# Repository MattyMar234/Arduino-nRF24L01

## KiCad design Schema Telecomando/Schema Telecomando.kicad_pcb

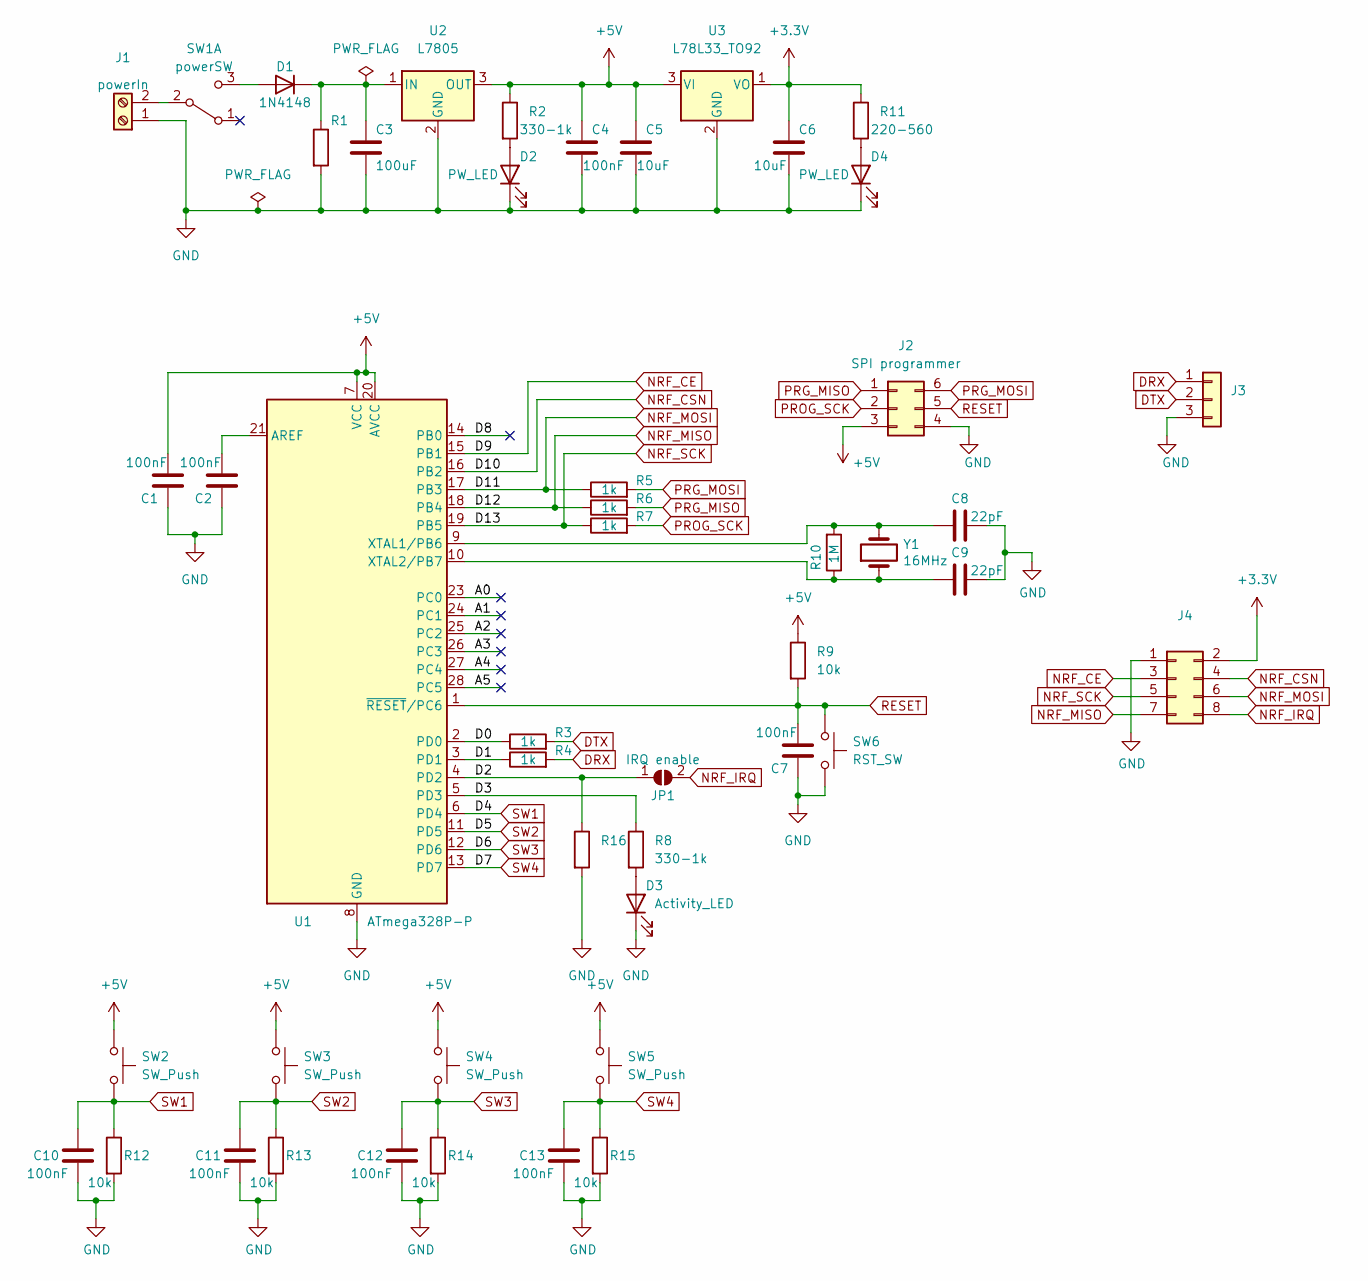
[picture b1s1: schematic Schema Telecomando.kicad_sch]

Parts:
C1, C2, C4, C7, C10, C11, C12, C13: 100nF; C_Disc_D7.0mm_W2.5mm_P5.00mm
C3: 100uF; CP_Radial_D8.0mm_P3.50mm
C5, C6: 10uF; CP_Radial_D8.0mm_P3.50mm
C8, C9: 22pF; C_Disc_D7.0mm_W2.5mm_P5.00mm
D1: 1N4148; D_DO-35_SOD27_P7.62mm_Horizontal
D2, D4: PW_LED; LED_D3.0mm
D3: Activity_LED; LED_D3.0mm
J1: powerIn; TerminalBlock_Altech_AK300-2_P5.00mm
J2: SPI programmer; PinHeader_1x06_P2.54mm_Horizontal
J3: PinHeader_1x03_P2.54mm_Horizontal
J4: (no value)
JP1: IRQ enable; SolderJumper-2_P1.3mm_Open_RoundedPad1.0x1.5mm
R1, R16: R_Axial_DIN0207_L6.3mm_D2.5mm_P10.16mm_Horizontal
R2, R8: 330-1k; R_Axial_DIN0207_L6.3mm_D2.5mm_P10.16mm_Horizontal
R3, R4, R5, R6, R7: 1k; R_Axial_DIN0207_L6.3mm_D2.5mm_P10.16mm_Horizontal
R9, R12, R13, R14, R15: 10k; R_Axial_DIN0207_L6.3mm_D2.5mm_P10.16mm_Horizontal
R10: 1M; R_Axial_DIN0207_L6.3mm_D2.5mm_P10.16mm_Horizontal
R11: 220-560; R_Axial_DIN0207_L6.3mm_D2.5mm_P10.16mm_Horizontal
SW1: powerSW; SW_CuK_JS202011CQN_DPDT_Straight
SW2, SW3, SW4, SW5: SW_Push; SW_PUSH-12mm
SW6: RST_SW; SW_Tactile_Straight_KSL0Axx1LFTR
U1: ATmega328P-P; DIP-28_W7.62mm
U2: L7805; TO-220-3_Horizontal_TabDown
U3: L78L33_TO92; TO-92_Inline
Y1: 16MHz; Crystal_HC18-U_Vertical

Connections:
+3V3: C6.1, J4.2, R11.1, U3.1 (VO); also elsewhere on the board
+5V: C1.2, C4.1, C5.1, J2.3, R2.1, R9.1, SW2.1, SW3.1, SW4.1, SW5.1, U1.7 (VCC), U1.20 (AVCC), U2.3 (OUT), U3.3 (VI); also elsewhere on the board
/A0: U1.23 (PC0)
/A1: U1.24 (PC1)
/A2: U1.25 (PC2)
/A3: U1.26 (PC3)
/A4: U1.27 (PC4)
/A5: U1.28 (PC5)
/D0: R3.1, U1.2 (PD0)
/D1: R4.1, U1.3 (PD1)
/D2: JP1.1 (A), R16.1, U1.4 (PD2)
/D3: R8.1, U1.5 (PD3)
/D8: U1.14 (PB0)
DRX: J3.1, R4.2
DTX: J3.2, R3.2
GND: C1.1, C2.1, C3.2, C4.2, C5.2, C6.2, C7.1, C8.1, C9.1, C10.1, C11.1, C12.1, C13.1, D2.1 (K), D3.1 (K), D4.1 (K), J1.1, J2.4, J3.3, J4.1, R1.2, R12.2, R13.2, R14.2, R15.2, R16.2, SW6.3 (B), SW6.4 (B), U1.8 (GND), U1.22 (GND), U2.2 (GND), U3.2 (GND); also elsewhere on the board
NRF_CE: J4.3, U1.15 (PB1); also elsewhere on the board
NRF_CSN: J4.4, U1.16 (PB2); also elsewhere on the board
NRF_IRQ: J4.8, JP1.2 (B); also elsewhere on the board
NRF_MISO: J4.7, R6.1, U1.18 (PB4); also elsewhere on the board
NRF_MOSI: J4.6, R5.1, U1.17 (PB3); also elsewhere on the board
NRF_SCK: J4.5, R7.1, U1.19 (PB5); also elsewhere on the board
unnamed: C2.2, U1.21 (AREF)
unnamed: C3.1, D1.1 (K), R1.1, U2.1 (IN)
unnamed: C8.2, R10.2, U1.9 (XTAL1/PB6), Y1.2
unnamed: C9.2, R10.1, U1.10 (XTAL2/PB7), Y1.1
unnamed: D1.2 (A), SW1.3 (C)
unnamed: D2.2 (A), R2.2
unnamed: D3.2 (A), R8.2
unnamed: D4.2 (A), R11.2
unnamed: J1.2, SW1.2 (B)
PRG_MISO: J2.1, R6.2
PRG_MOSI: J2.6, R5.2
PROG_SCK: J2.2, R7.2
RESET: C7.2, J2.5, R9.2, SW6.1 (A), SW6.2 (A), U1.1 (~RESET/PC6)
SW1: C10.2, R12.1, SW2.2, U1.6 (PD4); also elsewhere on the board
SW2: C11.2, R13.1, SW3.2, U1.11 (PD5); also elsewhere on the board
SW3: C12.2, R14.1, SW4.2, U1.12 (PD6); also elsewhere on the board
SW4: C13.2, R15.1, SW5.2, U1.13 (PD7); also elsewhere on the board

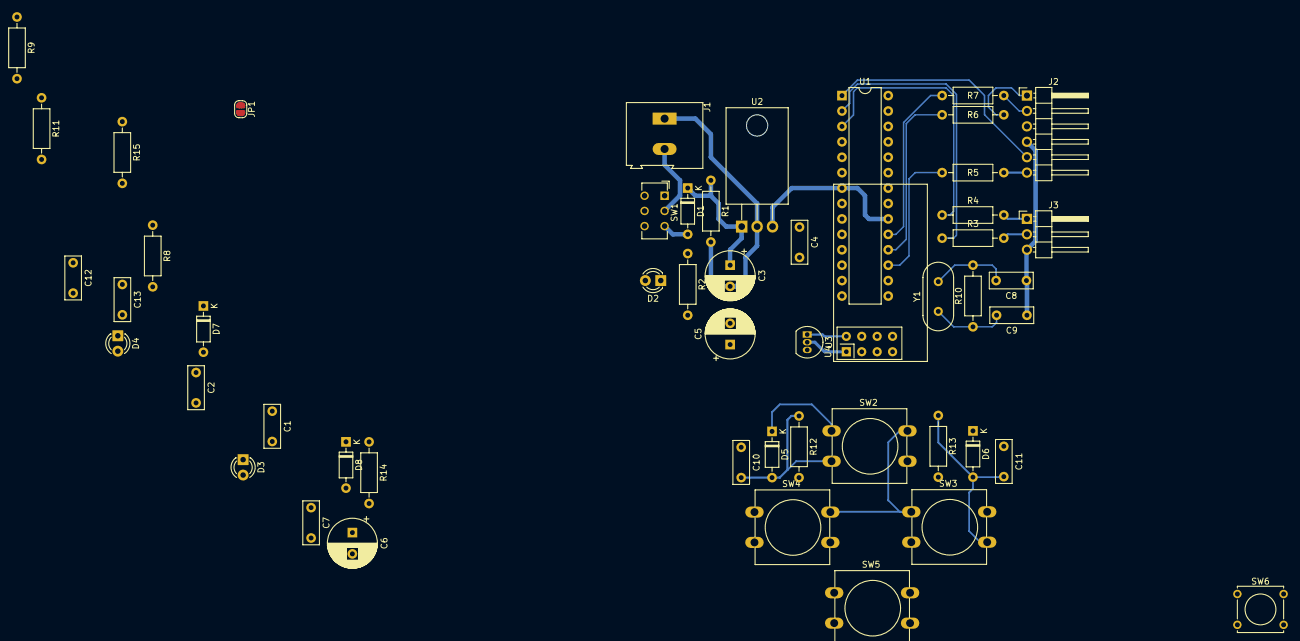
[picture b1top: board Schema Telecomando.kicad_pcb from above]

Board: 2 copper layers, 51 parts (0 on the bottom side), 32 nets.

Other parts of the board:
D5, D6, D7, D8: 1N4148; D_DO-35_SOD27_P7.62mm_Horizontal
U4: NRF24L01_Breakout; nRF24L01_Breakout

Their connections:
+3V3: U4.2 (VCC); also elsewhere on the board
+5V: D5.1 (K), D6.1 (K), D7.1 (K), D8.1 (K); also elsewhere on the board
GND: U4.1 (GND); also elsewhere on the board
NRF_CE: U4.3 (CE); also elsewhere on the board
NRF_CSN: U4.4 (~CSN); also elsewhere on the board
NRF_IRQ: U4.8 (IRQ); also elsewhere on the board
NRF_MISO: U4.7 (MISO); also elsewhere on the board
NRF_MOSI: U4.6 (MOSI); also elsewhere on the board
NRF_SCK: U4.5 (SCK); also elsewhere on the board
SW1: D5.2 (A); also elsewhere on the board
SW2: D6.2 (A); also elsewhere on the board
SW3: D7.2 (A); also elsewhere on the board
SW4: D8.2 (A); also elsewhere on the board

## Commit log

2023-09-18 Schema controller
2023-09-18 modifiche
2023-09-25 creazione classe controllers
2023-09-26 Aggiunto zener e power regulators
2023-10-02 name fixing
2023-10-03 rx fixing
2023-10-04 bug fix
2023-10-24 software reset
